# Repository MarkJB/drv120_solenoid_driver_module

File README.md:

# drv120_solenoid_driver_module

A small PCB module for efficiently driving a solenoid.

Rev B

Originally designed for use with drawing machines for fast up/down pen control but applicable to any project that involves driving a DC solenoid (as a guide > ~30 ohms). A TI DRV120 chip drives the solenoid with a configurable PWM frequency and takes care of the initial fast energize required to get the solenoid moving then ramps down the current to a lower level to hold the solenoid in place. Peak & keep (hold) current and PWM frequency are configurable with resistors and caps (see schematic and data sheet). 

Testing with the chosen solenoid (MCSMO-0603S12STD) resulted in using a 4.7uF capacitor for C1 (KEEP), 47K ohm resistor for R1 (PEAK) and a 0 ohm resisitor for R2 (OSC) for the default PWM frequency value (~20kHz).

See [datasheet](http://www.ti.com/lit/ds/symlink/drv120.pdf) for more details.

Rev B uses JST PH 2.00mm headers. If you are looking for a decent crimper that doesn't cost the earth, I can reccomend the [IWISS SN-2549](https://www.amazon.co.uk/gp/product/B01N4L8QMW/ref=as_li_tl?ie=UTF8&camp=1634&creative=6738&creativeASIN=B01N4L8QMW&linkCode=as2&tag=markjbenson-21&linkId=8a0828858f3374d5fcd8f459124a937a), available on Amazon for a lot less than the offical crimps. The litte extra jaws that jut out at the front do a decent job of crimping these small connectors.

# Buy a board
Buy from my [tindie store](https://www.tindie.com/products/edit/solenoid-driver-module-drv120-pwm-dc-6-24v/)

# Make a donation
If you find this project useful, consider donating.

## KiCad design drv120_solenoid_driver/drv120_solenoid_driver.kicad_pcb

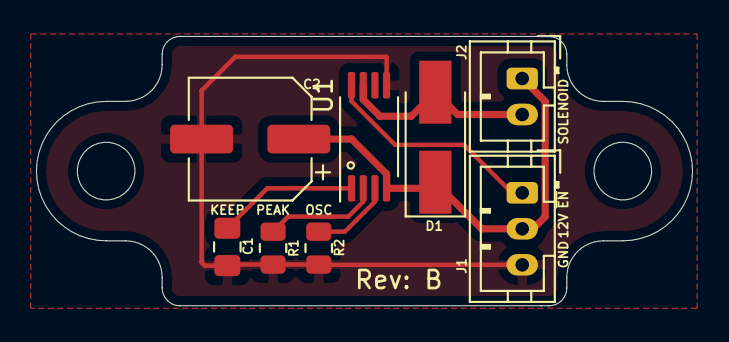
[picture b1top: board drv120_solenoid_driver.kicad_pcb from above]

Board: 2 copper layers, 36.4 x 15.0 mm, 8 parts (0 on the bottom side), 7 nets.

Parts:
C1: 1u; C_0805_2012Metric_Pad1.18x1.45mm_HandSolder
C2: 47u; CP_Elec_6.3x5.8
D1: D; D_SMA_Handsoldering
J1: PWR/EN; JST_PH_B3B-PH-K_1x03_P2.00mm_Vertical
J2: Solenoid; JST_PH_B2B-PH-K_1x02_P2.00mm_Vertical
R1, R2: 0; R_0805_2012Metric
U1: drv120; TSSOP-8_4.4x3mm_P0.65mm

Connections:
/Enable: J1.1, U1.8
GND: C1.2, C2.2, J1.3, R1.2, R2.2, U1.5
unnamed: C1.1, U1.1
unnamed: C2.1, D1.1, J1.2, J2.1, U1.4
unnamed: D1.2, J2.2, U1.7
unnamed: R1.1, U1.2
unnamed: R2.1, U1.3

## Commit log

2020-02-25 Single sided PCB
    First pass at a single sided PCB
2020-02-26 Single sided for engraver
2020-03-19 Double sided PCB v0.2
2020-03-20 Updated silk screen around connectors
2020-05-01 Add photo of prototype boards
2020-05-01 Add PDF of schematic
2021-10-21 Tab mounting version
    PCB design with mounting tabs on either side
2021-10-26 Changed to JST-PH 2.00 TH connectors
    Also changed input connector to a single 3 pin JST. Solenoid is on a 2 pin JST.
2021-10-26 Add production files
2021-11-10 Add component part numbers
2022-02-24 Add pin map, new images, schematic pdf and clean up old files
2022-02-24 Add tindie store link and paypal donation button
2022-02-24 Use shareable link/hosted button for paypal donate button.
2022-02-24 Add amazon affiliate link for IWISS crimpers
2022-02-24 Clean up
